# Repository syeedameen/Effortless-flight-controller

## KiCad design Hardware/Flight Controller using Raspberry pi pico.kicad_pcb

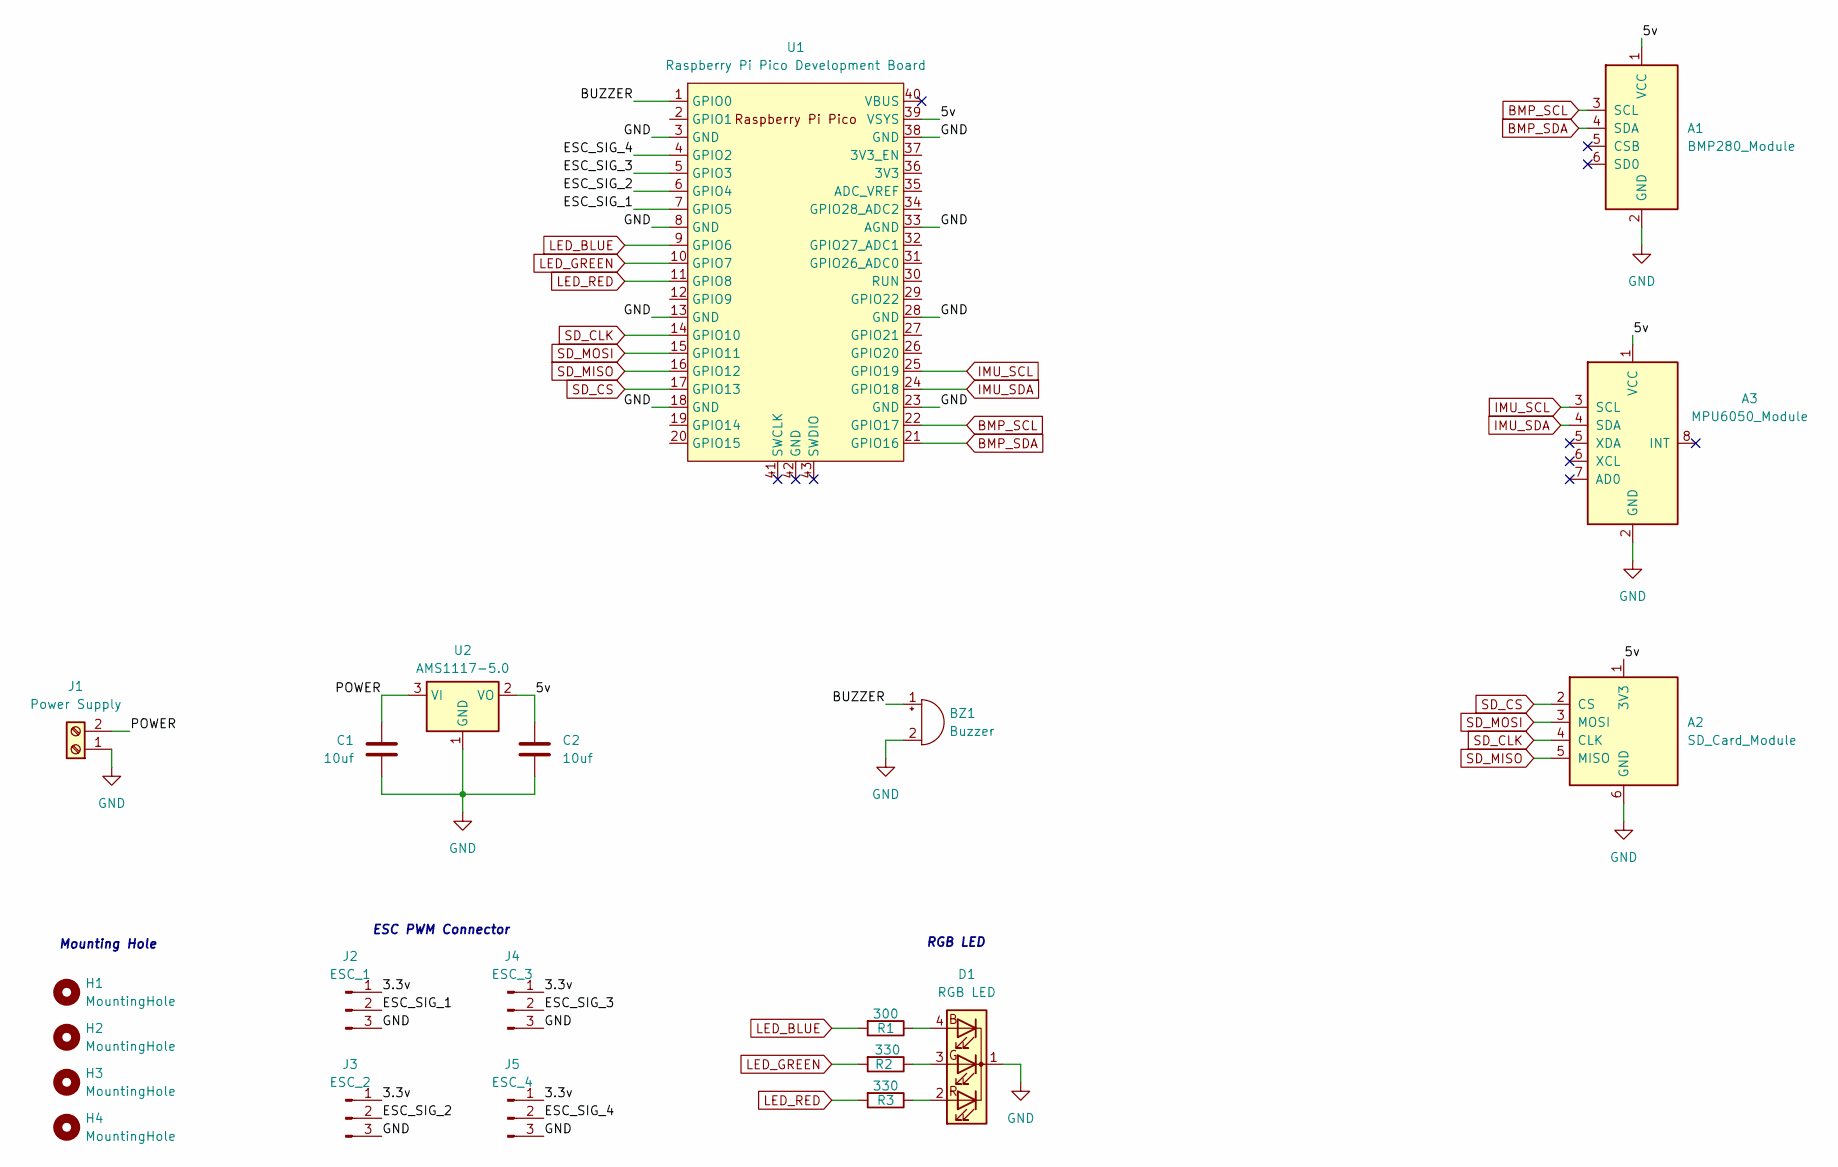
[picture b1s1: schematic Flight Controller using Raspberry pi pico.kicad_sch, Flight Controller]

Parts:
A1: BMP280_Module
A2: SD_Card_Module
A3: MPU6050_Module
BZ1: Buzzer; MagneticBuzzer_Kingstate_KCG0601
C1, C2: 10uf; CP_Radial_D8.0mm_P3.50mm
D1: RGB LED; LED_D5.0mm-4_RGB_Wide_Pins
H1, H2, H3, H4: MountingHole; MountingHole_3.5mm_Pad
J1: Power Supply; TerminalBlock_bornier-2_P5.08mm
J2: ESC_1; PinSocket_1x03_P2.54mm_Vertical
J3: ESC_2; PinSocket_1x03_P2.54mm_Vertical
J4: ESC_3; PinSocket_1x03_P2.54mm_Vertical
J5: ESC_4; PinSocket_1x03_P2.54mm_Vertical
R1: 300; R_Axial_DIN0204_L3.6mm_D1.6mm_P5.08mm_Horizontal
R2, R3: 330; R_Axial_DIN0204_L3.6mm_D1.6mm_P5.08mm_Horizontal
U1: Raspberry Pi Pico Development Board; RPi_Pico_SMD_TH
U2: AMS1117-5.0; SOT-223-3_TabPin2

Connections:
/3.3v: J2.1, J3.1, J4.1, J5.1
/5v: A1.1 (VCC), A2.1 (3V3), A3.1 (VCC), C2.1, U1.39 (VSYS), U2.2 (VO)
/BUZZER: BZ1.1 (+), U1.1 (GPIO0)
/ESC_SIG_1: J2.2, U1.7 (GPIO5)
/ESC_SIG_2: J3.2, U1.6 (GPIO4)
/ESC_SIG_3: J4.2, U1.5 (GPIO3)
/ESC_SIG_4: J5.2, U1.4 (GPIO2)
/POWER: C1.1, J1.2, U2.3 (VI)
BMP_SCL: A1.3 (SCL), U1.22 (GPIO17)
BMP_SDA: A1.4 (SDA), U1.21 (GPIO16)
GND: A1.2 (GND), A2.6 (GND), A3.2 (GND), BZ1.2 (-), C1.2, C2.2, D1.1 (K), J1.1, J2.3, J3.3, J4.3, J5.3, U1.3 (GND), U1.8 (GND), U1.13 (GND), U1.18 (GND), U1.23 (GND), U1.28 (GND), U1.33 (AGND), U1.38 (GND), U2.1 (GND)
IMU_SCL: A3.3 (SCL), U1.25 (GPIO19)
IMU_SDA: A3.4 (SDA), U1.24 (GPIO18)
LED_BLUE: R1.2, U1.9 (GPIO6)
LED_GREEN: R2.2, U1.10 (GPIO7)
LED_RED: R3.2, U1.11 (GPIO8)
unnamed: D1.4 (BA), R1.1
unnamed: D1.3 (GA), R2.1
unnamed: D1.2 (RA), R3.1
SD_CLK: A2.4 (CLK), U1.14 (GPIO10)
SD_CS: A2.2 (CS), U1.17 (GPIO13)
SD_MISO: A2.5 (MISO), U1.16 (GPIO12)
SD_MOSI: A2.3 (MOSI), U1.15 (GPIO11)

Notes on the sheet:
ESC PWM Connector
RGB LED
Mounting Hole

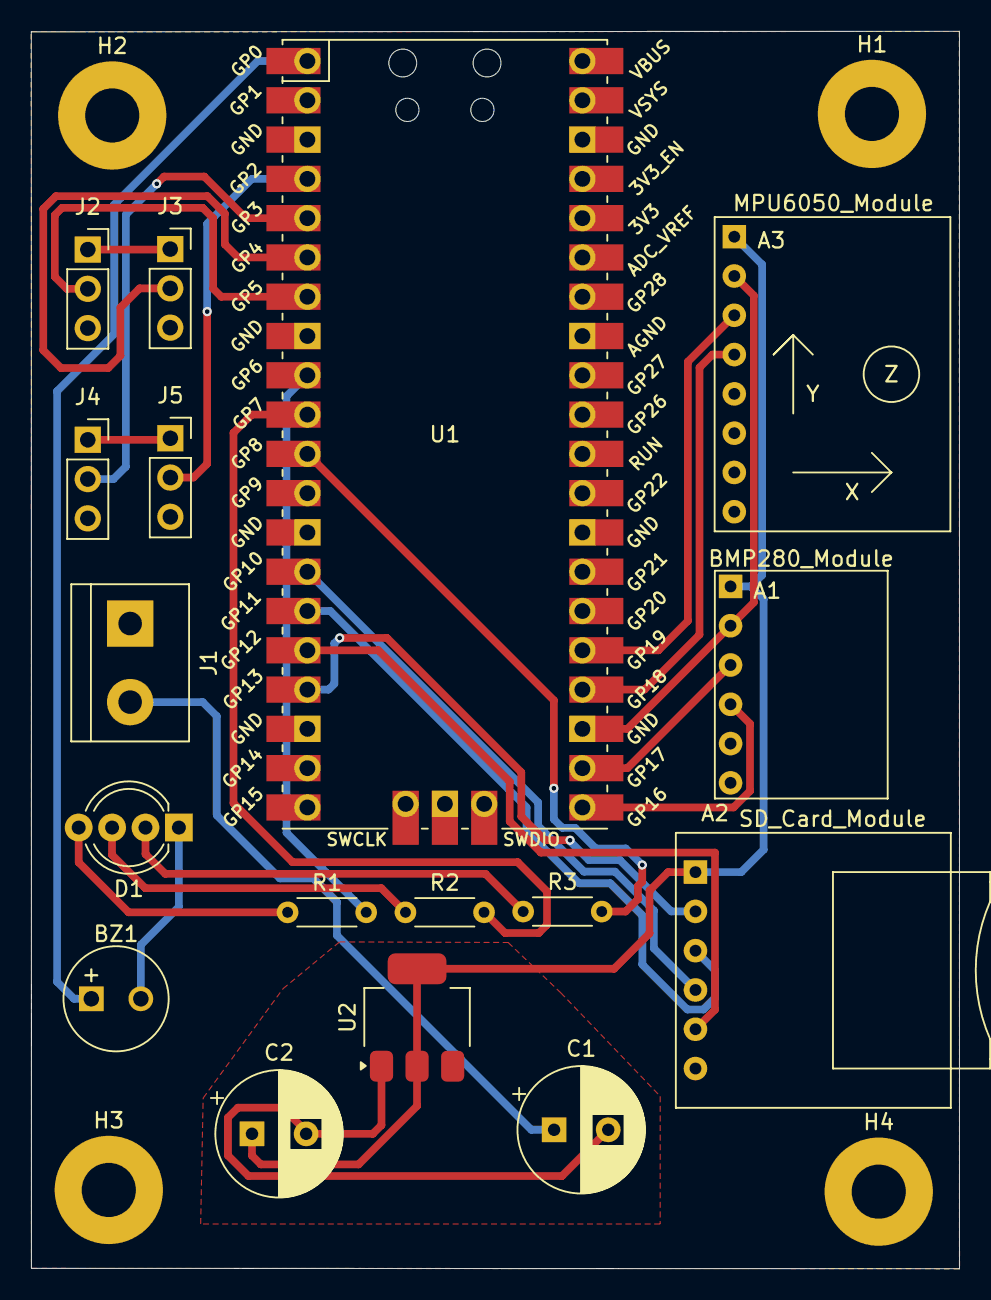
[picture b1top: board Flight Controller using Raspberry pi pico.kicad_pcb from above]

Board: 2 copper layers, 60.0 x 80.0 mm, 21 parts (0 on the bottom side), 23 nets.
